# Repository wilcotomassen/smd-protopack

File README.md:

# Breadboarding protopack

Pack of PCB's for (SMD) prototyping, designed in Eagle, geared towards cheap PCB services such as Seeed and Dirty PCBs (no affiliation). 
Target is to create a single pack of very usable proto board on a 10x10cm area.

Order it directly [here](http://dirtypcbs.com/store/designer/details/wjt/5832/protopack-gerbers-1-0-zip) from Dirty PCBs

# Boards included:

SMD breakout boards:
* TQFP32 IC
* SOIC16 / SSOP16 IC
* SOT23 / SOT89 IC
* SOT223 IC
* SOT23-5 IC
* 0805/0603 resistor/capacitor/led (3x)
* 0805 led with 0603 resistor (2x)

Other breakout boards:
* RJ45 breakout board
* DB9 Female breakout board
* DB9 Male breakout board
* 3 pin screw terminal breakout boards
* Momentary pushbutton (2x)
* Minimal 'Arduino'

Pogo pin tools:
* 1x6 FDTI adapter
* 2x3 AVR ICSP programming adapter

A correct Pogo pin for these boards is the P100-E2 1mm pogo pin, available here: http://dirtypcbs.com/store/details/12/dirty-pogo-pins

Other:
* 8x6 island style proto board

# Usage tips:

The boards can be fairly easily broken out of the panel on the holes. This will leave a rough spot, which can easily be trimmed with some sidecutting pliers or with a file or some sandpaper.

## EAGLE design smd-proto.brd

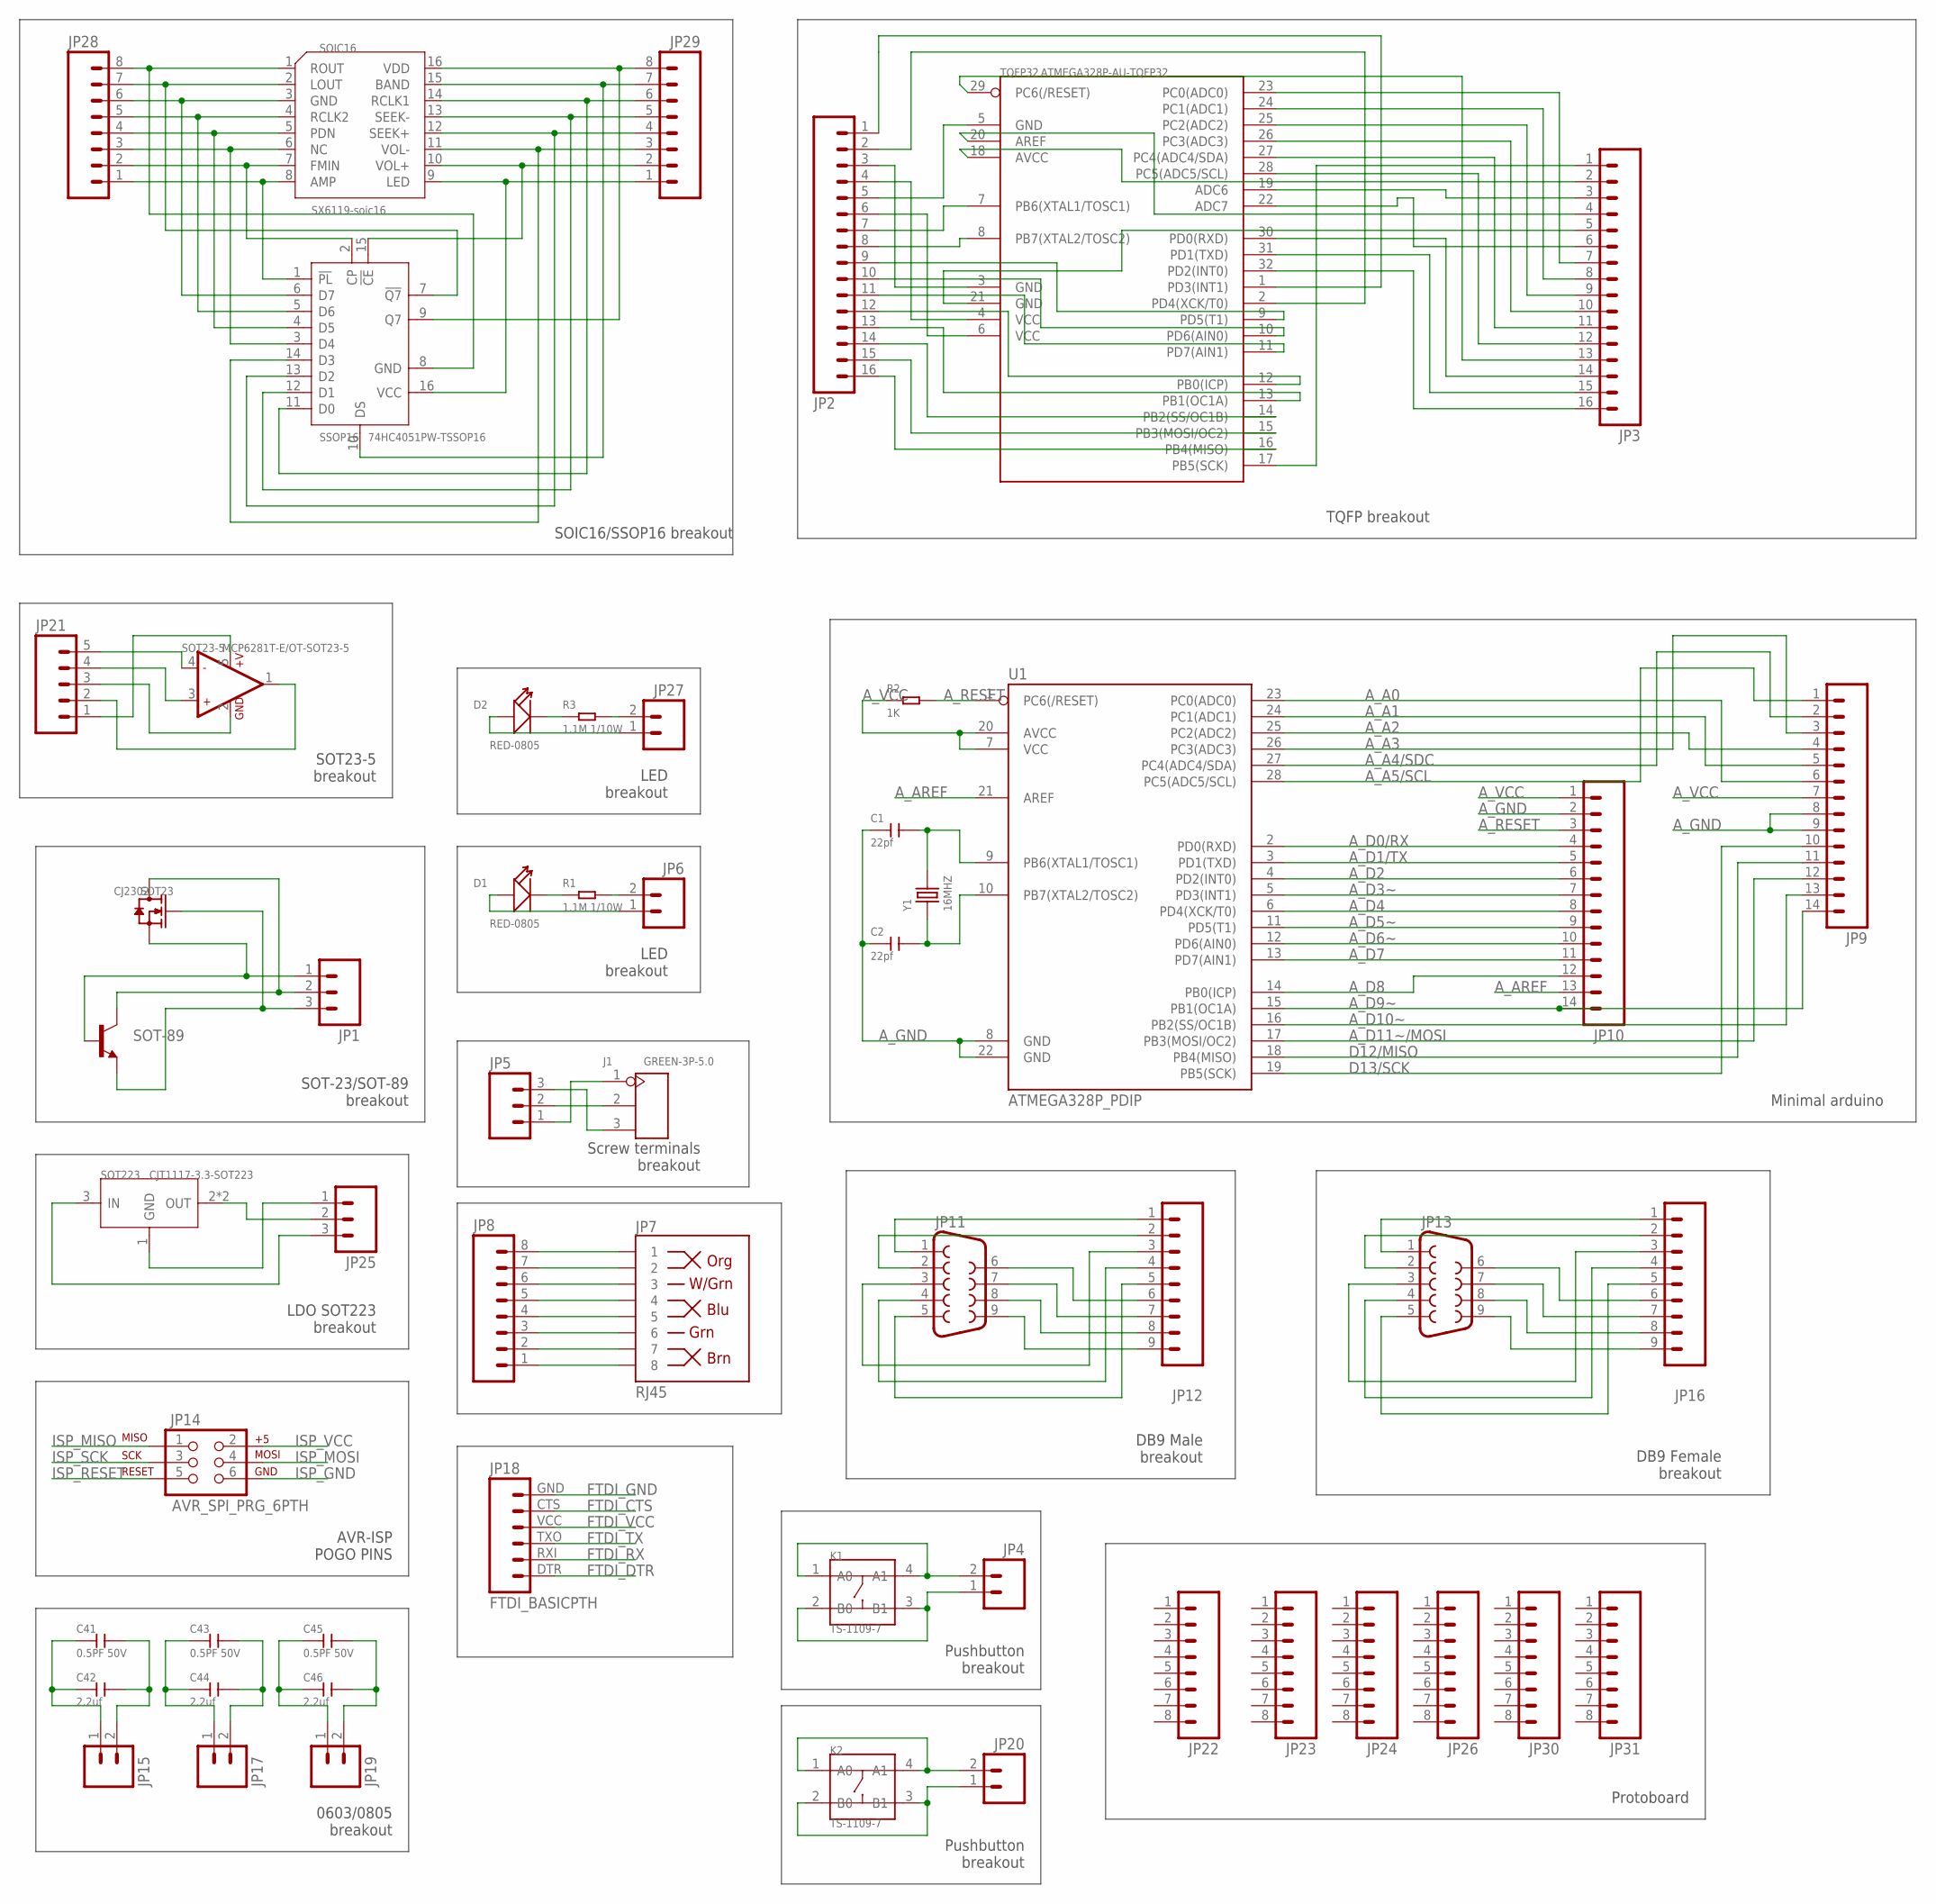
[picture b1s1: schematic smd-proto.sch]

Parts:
C1, C2: 22pf; C0603
C41, C43, C45: 0.5PF 50V; C0603
C42, C44, C46: 2.2uf; C0805
D1, D2: RED-0805; LED-0805
J1: GREEN-3P-5.0; H3-5.0-15.5X8.0MM
JP1, JP5, JP25: M03PTH; 1X03
JP2, JP3: M16PTH; 1X16
JP4, JP6, JP15, JP17, JP19, JP20, JP27: M02PTH; 1X02
JP7: RJ45; RJ45-8
JP8, JP28, JP29: M08; 1X08_ROUND
JP9, JP10: M14; 1X14
JP11: DB9MALE; DB9_MALE
JP12, JP16: M09; 1X09
JP13: DB9FEMALE; DB9
JP14: AVR_SPI_PRG_6PTH; 2X3
JP18: FTDI_BASICPTH; FTDI_BASIC
JP21: M05PTH; 1X05
JP22, JP23, JP24, JP26, JP30, JP31: M08NO_SILK_FEMALE_PTH; 1X08_NO_SILK
K1, K2: TS-1109-7; SW4-6.2X6.2X5.0MM
R1, R3: 1.1M 1/10W; R0603
R2: 1K; R0603
SOIC16: SX6119-soic16; SOIC16-1.27-10X3.9MM
SOT23: CJ2302; SOT-23
SOT23-5: MCP6281T-E/OT-SOT23-5; SOT-23-5
SOT223: CJT1117-3.3-SOT223; SOT-223
SOT-89: TRANSISTOR_NPNSOT89; SOT89
SSOP16: 74HC4051PW-TSSOP16; TSSOP16-0.65-5X4.4MM
TQFP32: ATMEGA328P-AU-TQFP32; TQFP32-0.8-7X7MM
U1: ATMEGA328P_PDIP; DIL28-3
Y1: 16MHZ; X2-SMD-5.0X3.2X1.3MM

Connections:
A_A0: JP9.6, U1.23 (PC0(ADC0))
A_A1: JP9.5, U1.24 (PC1(ADC1))
A_A2: JP9.4, U1.25 (PC2(ADC2))
A_A3: JP9.3, U1.26 (PC3(ADC3))
A_A4/SDC: JP9.2, U1.27 (PC4(ADC4/SDA))
A_A5/SCL: JP9.1, U1.28 (PC5(ADC5/SCL))
A_AREF: JP10.13, U1.21 (AREF)
A_D0/RX: JP10.4, U1.2 (PD0(RXD))
A_D1/TX: JP10.5, U1.3 (PD1(TXD))
A_D2: JP10.6, U1.4 (PD2(INT0))
A_D3~: JP10.7, U1.5 (PD3(INT1))
A_D4: JP10.8, U1.6 (PD4(XCK/T0))
A_D5~: JP10.9, U1.11 (PD5(T1))
A_D6~: JP10.10, U1.12 (PD6(AIN0))
A_D7: JP10.11, U1.13 (PD7(AIN1))
A_D8: JP10.12, U1.14 (PB0(ICP))
A_D9~: JP9.14, JP10.14, U1.15 (PB1(OC1A))
A_D10~: JP9.13, U1.16 (PB2(SS/OC1B))
A_D11~/MOSI: JP9.12, U1.17 (PB3(MOSI/OC2))
A_GND: C1.1, C2.1, JP9.8, JP9.9, JP10.2, U1.8 (GND), U1.22 (GND)
A_RESET: JP10.3, R2.2, U1.1 (PC6(/RESET))
A_VCC: JP9.7, JP10.1, R2.1, U1.7 (VCC), U1.20 (AVCC)
D12/MISO: JP9.11, U1.18 (PB4(MISO))
D13/SCK: JP9.10, U1.19 (PB5(SCK))
FTDI_CTS: JP18.CTS (5)
FTDI_DTR: JP18.DTR (1)
FTDI_GND: JP18.GND (6)
FTDI_RX: JP18.RXI (2)
FTDI_TX: JP18.TXO (3)
FTDI_VCC: JP18.VCC (4)
GND: JP28.8, SOIC16.1 (ROUT), SSOP16.8 (GND)
ISP_GND: JP14.6
ISP_MISO: JP14.1
ISP_MOSI: JP14.4
ISP_RESET: JP14.5
ISP_SCK: JP14.3
ISP_VCC: JP14.2
unnamed: JP21.5, SOT23-5.4 (-IN1)
unnamed: JP2.1, TQFP32.1 (PD3(INT1))
unnamed: JP2.2, TQFP32.2 (PD4(XCK/T0))
unnamed: JP2.3, TQFP32.3 (GND)
unnamed: JP2.4, TQFP32.4 (VCC)
unnamed: JP2.5, TQFP32.5 (GND)
unnamed: JP2.6, TQFP32.6 (VCC)
unnamed: JP2.7, TQFP32.7 (PB6(XTAL1/TOSC1))
unnamed: JP2.8, TQFP32.8 (PB7(XTAL2/TOSC2))
unnamed: JP2.9, TQFP32.9 (PD5(T1))
unnamed: JP2.11, TQFP32.11 (PD7(AIN1))
unnamed: JP2.10, TQFP32.10 (PD6(AIN0))
unnamed: JP2.12, TQFP32.12 (PB0(ICP))
unnamed: JP2.13, TQFP32.13 (PB1(OC1A))
unnamed: JP2.14, TQFP32.14 (PB2(SS/OC1B))
unnamed: JP21.2, SOT23-5.1 (OUT1)
unnamed: JP21.1, SOT23-5.5 (+V)
unnamed: JP2.15, TQFP32.15 (PB3(MOSI/OC2))
unnamed: JP21.4, SOT23-5.3 (+IN1)
unnamed: JP21.3, SOT23-5.2 (GND)
unnamed: JP1.3, SOT23.1 (G), SOT-89.3 (E)
unnamed: JP2.16, TQFP32.16 (PB4(MISO))
unnamed: JP1.2, SOT23.3 (D), SOT-89.2 (C)
unnamed: JP3.1, TQFP32.17 (PB5(SCK))
unnamed: JP3.2, TQFP32.18 (AVCC)
unnamed: JP29.6, SOIC16.14 (RCLK1), SSOP16.11 (D0)
unnamed: JP3.3, TQFP32.19 (ADC6)
unnamed: JP3.4, TQFP32.20 (AREF)
unnamed: JP3.5, TQFP32.21 (GND)
unnamed: JP3.6, TQFP32.22 (ADC7)
unnamed: JP3.7, TQFP32.23 (PC0(ADC0))
unnamed: JP3.8, TQFP32.24 (PC1(ADC1))
unnamed: JP3.9, TQFP32.25 (PC2(ADC2))
unnamed: JP3.10, TQFP32.26 (PC3(ADC3))
unnamed: JP3.11, TQFP32.27 (PC4(ADC4/SDA))
unnamed: JP3.12, TQFP32.28 (PC5(ADC5/SCL))
unnamed: JP3.13, TQFP32.29 (PC6(/RESET))
unnamed: JP3.14, TQFP32.30 (PD0(RXD))
unnamed: JP3.15, TQFP32.31 (PD1(TXD))
unnamed: JP3.16, TQFP32.32 (PD2(INT0))
unnamed: JP4.1, K1.2 (B0), K1.3 (B1)
unnamed: JP29.3, SOIC16.11 (VOL-), SSOP16.14 (D3)
unnamed: C41.1, C42.1, JP15.1
unnamed: C41.2, C42.2, JP15.2
unnamed: C43.1, C44.1, JP17.1
unnamed: C43.2, C44.2, JP17.2
unnamed: C45.1, C46.1, JP19.1
unnamed: JP28.7, SOIC16.2 (LOUT), SSOP16.7 (!Q7)
unnamed: JP28.2, SOIC16.7 (FMIN), SSOP16.2 (CP)
unnamed: C45.2, C46.2, JP19.2
unnamed: JP29.7, SOIC16.15 (BAND), SSOP16.10 (DS)
unnamed: JP4.2, K1.1 (A0), K1.4 (A1)
unnamed: JP29.5, SOIC16.13 (SEEK-), SSOP16.12 (D1)
unnamed: JP29.4, SOIC16.12 (SEEK+), SSOP16.13 (D2)
unnamed: D1.+, JP6.1
unnamed: D1.-, R1.1
unnamed: JP28.6, SOIC16.3 (GND), SSOP16.6 (D7)
unnamed: JP6.2, R1.2
unnamed: JP28.5, SOIC16.4 (RCLK2), SSOP16.5 (D6)
unnamed: J1.2, JP5.2
unnamed: J1.1, JP5.1
unnamed: J1.3, JP5.3
unnamed: JP7.1, JP8.8
unnamed: JP7.2, JP8.7
unnamed: JP7.3, JP8.6
unnamed: JP7.4, JP8.5
unnamed: JP7.5, JP8.4
unnamed: JP7.6, JP8.3
unnamed: JP7.7, JP8.2
unnamed: JP1.1, SOT23.2 (S), SOT-89.1 (B)
unnamed: JP28.4, SOIC16.5 (PDN), SSOP16.4 (D5)
unnamed: JP7.8, JP8.1
unnamed: C1.2, U1.9 (PB6(XTAL1/TOSC1)), Y1.2
unnamed: C2.2, U1.10 (PB7(XTAL2/TOSC2)), Y1.1
unnamed: JP28.3, SOIC16.6 (NC), SSOP16.3 (D4)
unnamed: JP11.1, JP12.1
unnamed: JP11.2, JP12.2
unnamed: JP11.3, JP12.3
unnamed: JP11.4, JP12.4
unnamed: JP28.1, SOIC16.8 (AMP), SSOP16.1 (!PL)
unnamed: JP11.5, JP12.5
unnamed: JP11.6, JP12.6
unnamed: JP11.7, JP12.7
unnamed: JP11.8, JP12.8
unnamed: JP11.9, JP12.9
unnamed: JP13.1, JP16.1
unnamed: JP13.2, JP16.2
unnamed: JP13.3, JP16.3
unnamed: JP13.4, JP16.4
unnamed: JP13.5, JP16.5
unnamed: JP13.6, JP16.6
unnamed: JP13.7, JP16.7
unnamed: JP13.8, JP16.8
unnamed: JP13.9, JP16.9
unnamed: JP29.2, SOIC16.10 (VOL+), SSOP16.15 (!CE)
unnamed: JP20.1, K2.2 (B0), K2.3 (B1)
unnamed: JP20.2, K2.1 (A0), K2.4 (A1)
unnamed: D2.+, JP27.1
unnamed: D2.-, R3.1
unnamed: JP25.2, SOT223.2 (OUT), SOT223.TER (OUT)
unnamed: JP27.2, R3.2
unnamed: JP29.8, SOIC16.16 (VDD), SSOP16.9 (Q7)
unnamed: JP25.1, SOT223.1 (GND)
unnamed: JP25.3, SOT223.3 (IN)
VCC: JP29.1, SOIC16.9 (LED), SSOP16.16 (VCC)

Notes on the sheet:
SOIC16/SSOP16 breakout
SOT-23/SOT-89 breakout
LDO SOT223 breakout
SOT23-5 breakout
AVR-ISP POGO PINS
0603/0805 breakout
LED breakout
Pushbutton breakout
Screw terminals breakout
DB9 Male breakout
DB9 Female breakout
Minimal arduino
TQFP breakout
Protoboard

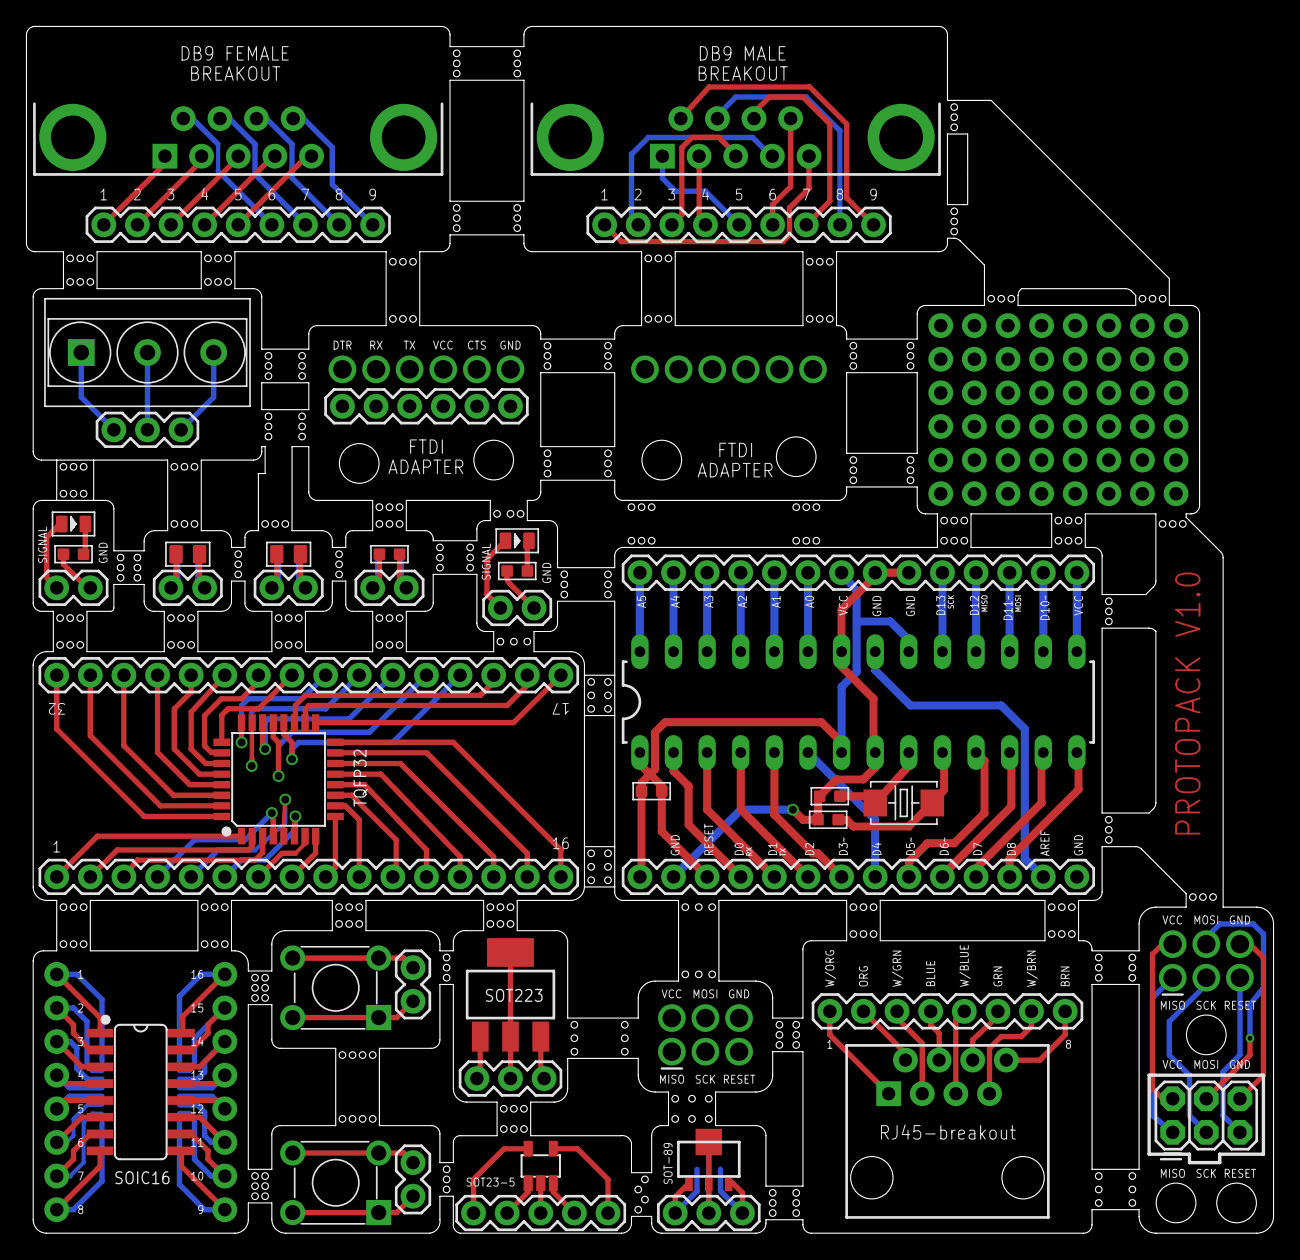
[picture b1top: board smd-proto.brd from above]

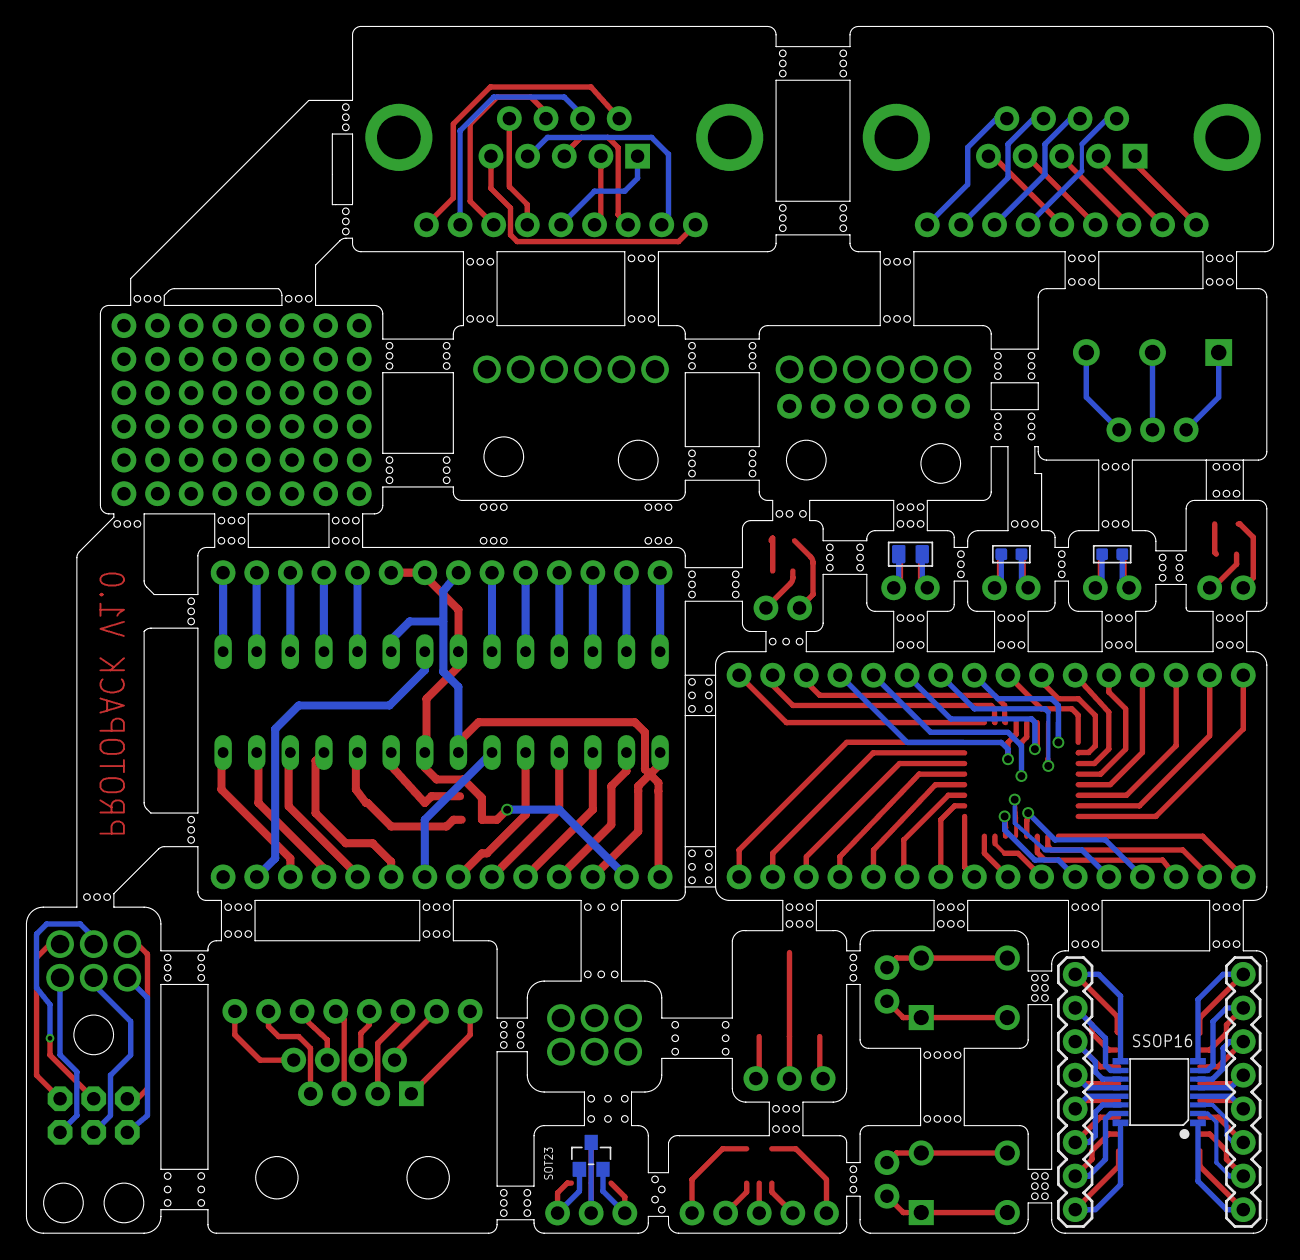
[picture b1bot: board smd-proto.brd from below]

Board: 2 copper layers, 94.2 x 91.2 mm, 56 parts (7 on the bottom side), 130 nets.

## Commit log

2017-02-07 Added gitignore and the initial brd and sch files
2017-02-07 Added Readme
2017-08-14 Added bunch of boards and outline
2017-08-15 Fixed ERC and DRC issues, finalized some boards
2017-11-16 Added dirtypcbs link
2017-11-16 Fixed buy link
2018-04-26 Added images

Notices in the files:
parts and their libraries:
SparkFun-Connectors: Licensing: Creative Commons ShareAlike 4.0 International - https://creativecommons.org/licenses/by-sa/4.0
